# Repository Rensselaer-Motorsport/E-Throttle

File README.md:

# E-Throttle
##Rensselaer Motorsports 

Everything related to the throtttle-by-wire system designed for RM21.

###Folders:
Board - Diptrace, KiCAD and related files for E-Throttle PCB board design

Communication - Python Scripts and stuff that will allow us to get data from/send instructions to the mainboard

PSoC - All PSoC code and designs to run the e-throttle system mainboard

---
###Contact:
Mitchell Mellone (mellom3@rpi.edu) for more information.

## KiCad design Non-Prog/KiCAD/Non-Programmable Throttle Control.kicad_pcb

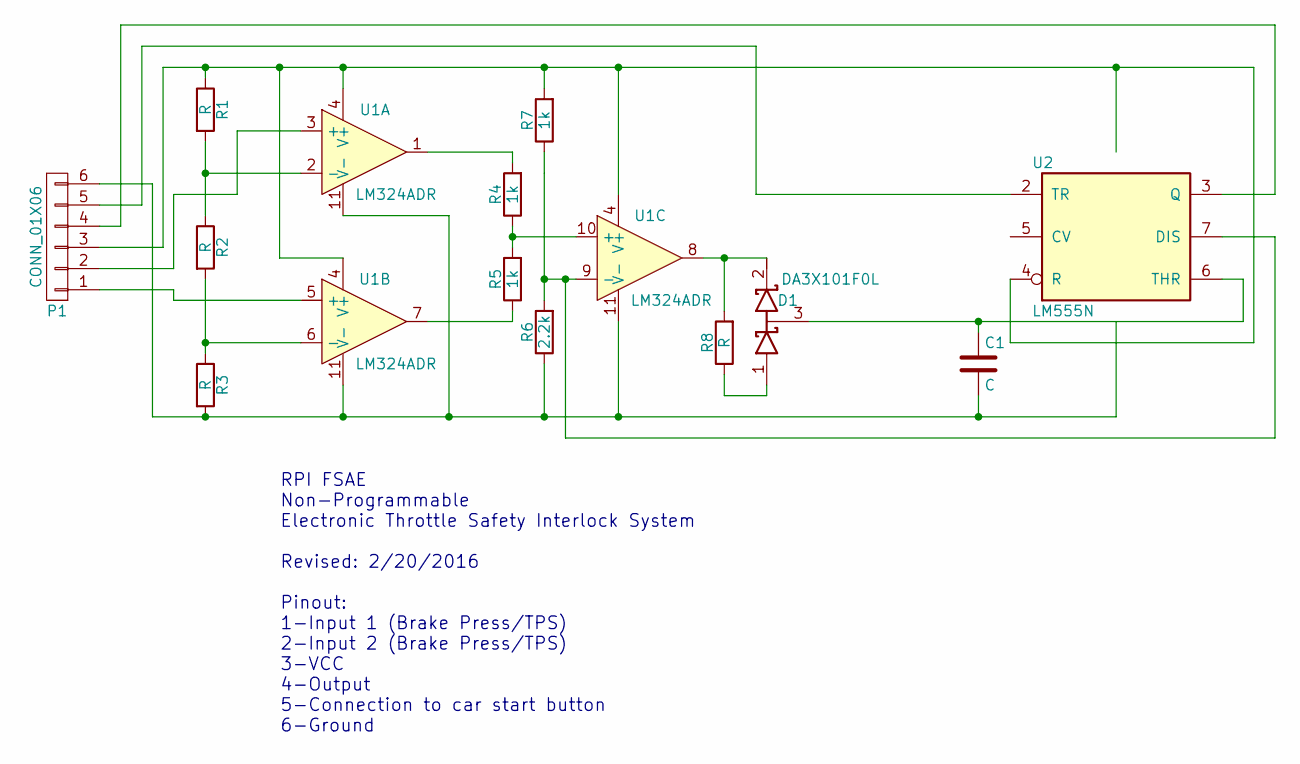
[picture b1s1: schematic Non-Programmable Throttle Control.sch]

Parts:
C1: C; C_0603
D1: DA3X101F0L; SOT-23
P1: CONN_01X06; Pin_Header_Straight_1x06
R1, R2, R3, R8: R; R_0603
R4, R5, R7: 1k; R_0603
R6: 2.2k; R_0603
U1: LM324ADR; SOIC-14_3.9x8.7mm_Pitch1.27mm
U2: LM555N; SOIC-8_3.9x4.9mm_Pitch1.27mm

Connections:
GND: C1.2, P1.6, R3.2, R6.1, U1.11 (V-), U2.1 (GND)
unnamed: C1.1, D1.3 (common), U2.6 (THR)
unnamed: D1.1 (A), R8.1
unnamed: D1.2 (K), R8.2, U1.8
unnamed: P1.1, U1.5 (+)
unnamed: P1.2, U1.3 (+)
unnamed: P1.4, U2.3 (Q)
unnamed: P1.5, U2.2 (TR)
unnamed: R1.2, R2.1, U1.2 (-)
unnamed: R2.2, R3.1, U1.6 (-)
unnamed: R4.1, R5.2, U1.10 (+)
unnamed: R4.2, U1.1
unnamed: R5.1, U1.7
unnamed: R6.2, R7.1, U1.9 (-), U2.7 (DIS)
VCC: P1.3, R1.1, R7.2, U1.4 (V+), U2.4 (R), U2.8 (VCC)

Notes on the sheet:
RPI FSAE Non-Programmable Electronic Throttle Safety Interlock System Revised: 2/20/2016 Pinout: 1-Input 1 (Brake Press/TPS) 2-Input 2 (Brake Press/TPS) 3-VCC 4-Output 5-Connection to car start button 6-Ground

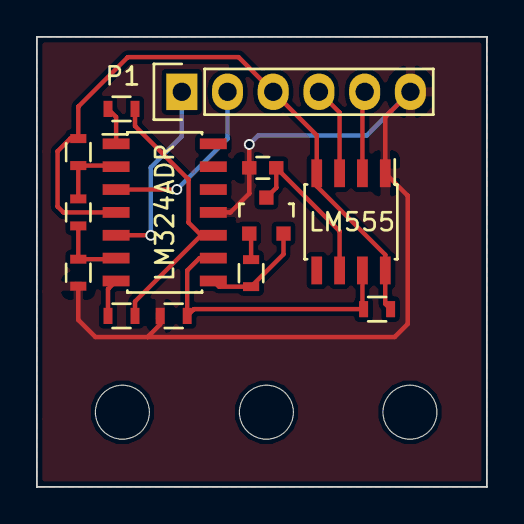
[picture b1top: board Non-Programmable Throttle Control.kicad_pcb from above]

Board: 2 copper layers, 25.0 x 25.0 mm, 13 parts (0 on the bottom side), 15 nets.

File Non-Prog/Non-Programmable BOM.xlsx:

Op-Amp |  | https://www.digikey.com/product-detail/en/LM324ADR/296-9540-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
555 Timer |  | https://www.digikey.com/product-detail/en/ICM7555CBAZ/ICM755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
Diode Pair |  | https://www.digikey.com/product-detail/en/DA3X101F0L/DA3X101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
Resistors |  | Mercer Lab
Capacitors |  | Mercer Lab

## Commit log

2015-11-14 init commit
2015-11-14 Potentiometer affects LED light
2015-11-15 Pass potentiometer data out through UART
2015-11-15 created project for mainboard and populated top design with ADCs for TPS and APPS
2015-11-15 Created local_handling to handle data and error checking for the TPS/APPS arrays
2015-12-05 Inital PCB schematic + design without traces:
2015-12-28 re-organized/re-started code
2015-12-29 started implementing signal_processing functions
2016-01-18 Getting data from pots should be more or less working
2016-01-21 tested queue and fixed bugs
2016-01-25 recommended changes made
2016-01-30 added new pcb layout design
2016-02-01 Updated the error_queue and placed a timer componenet
2016-02-04 Wrote global_implausibility function and updated error_buffer/queue to handle brake implausibilities. Did NOT update main.c, that definitely needs some work...
2016-02-07 updated with suggested changes
2016-02-12 test commit by dan
2016-02-13 PCB changes: servo power + GND added, Debug reformatted, analog input out of range run through voltage divider, UART added
2016-02-13 Updated error checking, switched timer and PWM to Fixed Function (from UDB). Cleaned up some code.
2016-02-13 Cleaned up the repo, big time
2016-02-13 Add logo for readme
2016-02-16 Added Non-Programmable Board Gerber Files
2016-02-17 Added KiCad Files
2016-02-17 Added BOM
    It's the BOM, dude.
2016-02-17 new PCB layout added with wider traces + other fixes
2016-02-20 newer version, rerouted - wider traces
2016-02-21 Updated Details, Added pinout to schematic
2016-02-21 Re-Netlisted
2016-02-21 Updated Details
2016-02-24 re-routed board to move caps closer + make board smaller
2016-02-28 updated schematic, smallest PCB layout!
2016-03-02 Updated PCB Files
2016-03-06 made mounting holes reasonable size, routed power + routed ground better
2016-03-07 connected ground net, resized mmounting holes and fixed copper pours
2016-03-08 Gerber files for E-throttle board
2016-03-09 moved lables to make yuriy happy
2016-03-09 BOM added
2016-03-15 updated communication to use basic padding
2016-03-15 Kinda a big commit, added a function to E-Throttle project that controls servo. Servo example stuff in Misc-Tests, PSoC_Eye, etc. (I should definitely clean that up...)
2016-03-15 Added Stencil
2016-04-09 made a basic gui to display e-throttle state
2016-04-09 wip, just cleaning out the add queue
2016-06-15 added new header and source files for comms
2016-06-16 added psoc test case for communication dev
2016-06-26 got the general communication stream working
2016-07-23 cleaned up comm test code in dev branch
2016-07-26 Moved constants from signal processing header to the constant header (because that makes more sense to me at this point in time)
2016-07-26 Created a bool type because its the 21st century, also reorganized some small things...
2016-07-26 Updated .gitignore to ignore all of the stupid autogenerated PSoC stuff, so now we'll have to build the project each time we pull, but the commits will be 100000000x nicer
2016-07-29 Got basic output over UART for testing
2016-07-31 basic test with no errors work. still some issues, primarily with timer, need to investigate
2016-09-02 Some timer updates
